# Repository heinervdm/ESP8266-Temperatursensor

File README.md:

# ESP8266-Temperatursensor
Wifi temperature sensor based on the Espressif ESP8266 Wifi module and the Dallas DS18X20 temperature sensor

For this project it is assumed, that the ESP8266 is configured for deep sleep. For e.g. ESP-01 one needs to patch to PCB, for ESP-03 one has to close the solder jumper neer pin 8.

To compile you have to adjust the paths in the Makefile and copy user_config.h.template to user_config.h and adjust the defines inside.
I'm using a hardcoded IP address because the DNS was not working very well for me and therefore consumes to much power.

The Firmware will read all connected DS18X20 sensors (A define in user_config.h determines the maximum amount of sensors) and will call a the path: /index.php?value[]=...&uid[]=...&... with the read temperature and the uid of the corresponding sensor, as well as the current supply voltage of the ESP8266 module and it's mac address as uid.

# This is based on the following projects:

DS18X20 readout: http://siwawi.bauing.uni-kl.de/avr_projects/tempsensor/

Makefile & user_main structure: https://github.com/esp8266/source-code-examples

ESP8266 eagle footprint: https://github.com/wvanvlaenderen/ESP8266-Eagle_Library

Javascript plotting: https://github.com/dima117/Chart.Scatter

BMP180 readout: https://github.com/reaper7/esp8266_i2c_bmp180

DHT11/22 readout: https://github.com/mathew-hall/esp8266-dht

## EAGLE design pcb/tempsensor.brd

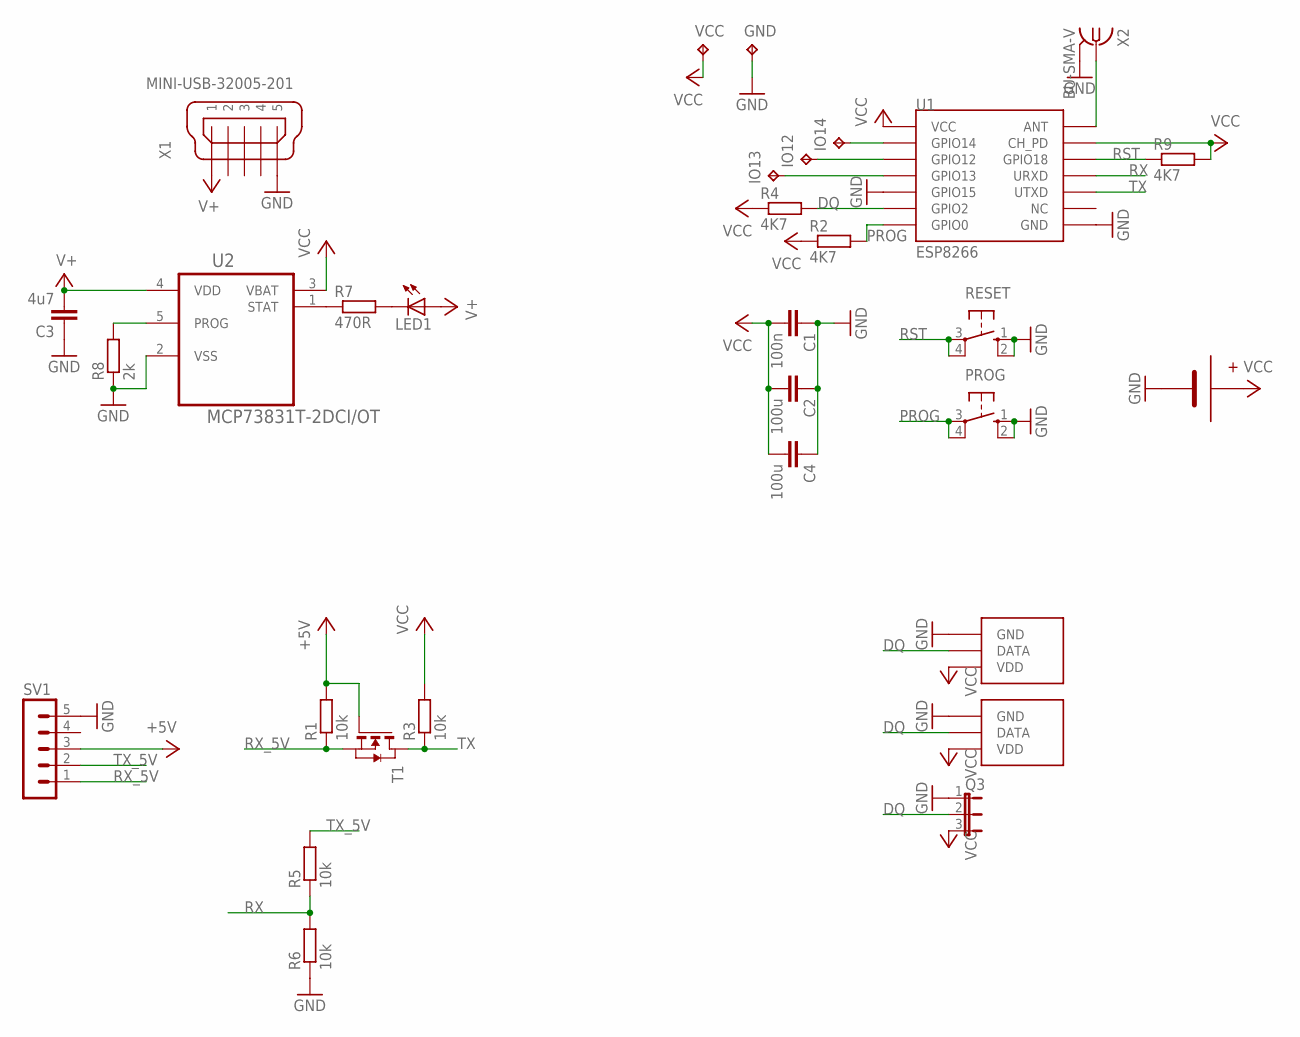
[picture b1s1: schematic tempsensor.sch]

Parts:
C1: 100n; C0805
C2, C4: 100u; C1206
C3: 4u7; C0805
GND: TPPAD1-13; P1-13
IO12, IO13, IO14: TPPAD1-13; P1-13
LED1: LEDCHIPLED_0805; CHIPLED_0805
PROG: 10-XX; B3F-10XX
Q1: DS18X20TO92; TO92
Q2: DS18X20SO-8; SO08WIDE
Q3: JP2E; JP2
R1, R3, R5, R6: 10k; M0805
R2, R4, R9: 4K7; M0805
R7: 470R; M0805
R8: 2k; M0805
RESET: 10-XX; B3F-10XX
SV1: MA05-1
T1: NMOSSOT23; SOT-23
U1: ESP8266; ESP-03
U2: MCP73831T-2DCI/OT; SOT95P270X145-5N
U$2: 18650-BATTERHOLDERHA1X18650; HA1X18650
VCC: TPPAD1-13; P1-13
X1: MINI-USB-32005-201; 32005-201
X2: BU-SMA-V

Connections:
+5V: R1.2, SV1.3, T1.3 (G)
DQ: Q1.2 (DATA), Q2.4 (DATA), Q3.2, R4.2, U1.GPIO2
GND: C1.1, C2.1, C3.1, C4.1, GND.TP, PROG.1 (S), PROG.2 (S1), Q1.3 (GND), Q2.5 (GND), Q3.1, R6.1, R8.1, RESET.1 (S), RESET.2 (S1), SV1.5, U1.GND, U1.GPIO15, U2.2 (VSS), U$2.P$1, X1.5, X2.2, X2.3 (2), X2.4 (2), X2.5 (2)
unnamed: R7.1, U2.1 (STAT)
unnamed: IO13.TP, U1.GPIO13
unnamed: IO12.TP, U1.GPIO12
unnamed: IO14.TP, U1.GPIO14
unnamed: LED1.C, R7.2
unnamed: R8.2, U2.5 (PROG)
unnamed: U1.ANT, X2.1
PROG: PROG.3, PROG.4 (P1), R2.2, U1.GPIO0
RST: R9.1, RESET.3, RESET.4 (P1), U1.GPIO18
RX: R5.1, R6.2, U1.URXD
RX_5V: R1.1, SV1.1, T1.2 (S)
TX: R3.1, T1.1 (D), U1.UTXD
TX_5V: R5.2, SV1.2
V+: C3.2, LED1.A, U2.4 (VDD), X1.1
VCC: C1.2, C2.2, C4.2, Q1.1 (VDD), Q2.3 (VDD), Q3.3, R2.1, R3.2, R4.1, R9.2, U1.CH_PD, U1.VCC, U2.3 (VBAT), U$2.P$2, VCC.TP

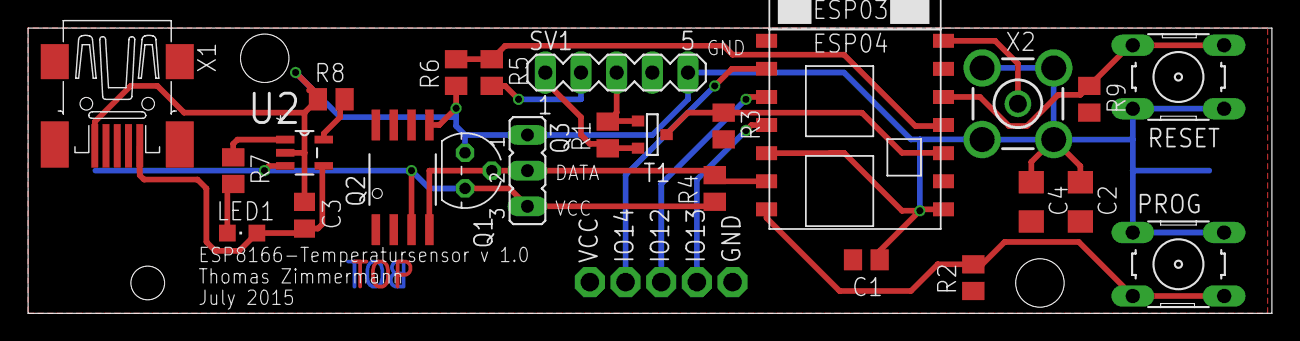
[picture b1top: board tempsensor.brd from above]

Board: 2 copper layers, 88.6 x 20.3 mm, 31 parts (1 on the bottom side), 18 nets.

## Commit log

2015-07-19 Commit inital version
2015-07-19 Update README.md
    Add links to sources of this project
2015-07-19 Update PCB
2015-07-19 Update PCB: Add lipo charging circuit based on mcp73831 and Reset und Program buttons
2015-07-19 PCB add library for MCP73831 from farnell
2015-07-19 PCB: add optional pullup resistor for RESET pin, and additional 100u cap for power
2015-07-19 Webpage: add option to modify and delete values, add checkboxes to show and hide values in the graph, disable animation of graph
2015-07-19 Add kind of deep discharge protection
2015-07-31 add a deploy.php to update the webpage automatically with github
2015-08-01 remove whoami and $PWD from deploy
2015-08-02 nicely format forms
2015-08-03 Add links to increase or decrease starttime
2015-08-03 fix missing $
2015-08-03 fix conversion of array to url
2015-08-03 Add missing )
2015-08-03 add missing parathese
2015-08-03 use correct key while putting together the url
2015-08-03 use correct starttime
2015-08-03 Nicer format for start and endtime links
2015-08-03 correct left and right single arrows
2015-08-03 align start and endtime links
2015-08-03 correct chart id
2015-08-03 tweak the css a little bit
2015-08-03 tweak css further
2015-08-10 fix zero padding in url call
2015-08-15 Fix Footprint for DS18B20, VCC and GND were swaped
2015-08-15 PCB: increase size of batterholder pads and rotate esp-03 so that it's antenna is no longer shielded
2015-08-16 Add a wifi scan after startup
2015-08-16 Don't check for random mac addr, fixes the problem that the ESP ist constantly reconnecting with reason 201
2015-08-16 Webpage: fix problem when daemonid is not yet known
2015-08-16 Disable ap scan, it needs to much time
2015-08-16 webpage: fix edit and delete prepared stmt
2015-10-03 Add SDK path to PATH before calling esptool
2015-10-03 update espmissingincludes.h for SDK version 1.4.0
    (copied from libesphttpd)
2015-10-03 call deepsleep also when connection failed
2015-12-06 PCB: rename testpoints, add points for VCC and GND, add RP-SMA connector for external antenna
2015-12-06 Add libraries for DHT11/22 humidity sensors and BMP180 pressure sensor
2015-12-06 Port to SDK version 1.5.0
2015-12-06 Add missing functions for dht library
2015-12-06 Add readout for DHT and BMP sensor and make everything configureable in user_config.h
2015-12-06 Update README.md
    Add more references
2015-12-11 Add ICACHE_FLASH_ATTR to various functions
2015-12-12 i2c_bmp180.c: cleanup
2015-12-12 user_main: fix bmp180 readout (i2c_init was missing), scale results to deg C and hPa
2015-12-12 fix dht readout
2016-01-05 disable wifi after deep sleep und reenable it again by calling wifi_station_connect after system_init is done
2016-01-09 Remove disabling of RF on startup again. Add timer which goes to deep sleep again, if the module is not connected within 10 seconds after wakeup
2016-04-27 webpage: Add index for value table
2016-04-27 Change sqlite database format
2016-04-27 remove alter table commands
2016-04-27 use unixtime column instead of time column
2016-04-27 Also use unixtime column as output
2016-09-30 Switch from SQLite class to PDO
2016-09-30 remove leftover call from SQLite class to finalize
2016-09-30 fix calls to fetchArray
2018-05-21 Make database type configureable
2018-05-21 Properly handle PDO::query
2018-05-21 Use prepared statement instead of query
2018-05-21 ADD support for ADS1115, move to SDK 2.1
2018-05-21 PDO connection has no close method...
2018-05-21 Use correct function to get unix timestamp for MySQL
2018-05-21 Add debug output
2018-05-21 Invert if
2018-05-21 Add more debug output
2018-05-21 Fix timezone conversion in mysql query
2018-05-21 Remove additional braket
2018-05-21 Use datetime to format date
2018-05-21 Fix table query to properly order the entries
2018-05-27 Move calibration from ESP to webpage
2018-05-27 Query calibration function from correct table
